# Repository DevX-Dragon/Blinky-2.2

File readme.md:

# Blinky 2.2
This is an blinky board by the NE555P chip. It has an potentiometer to control speed!.

## Layouts

## BOM

| Name | Quanity |
| --- | --- |
| NE555P | 1 |
| CD4017 | 1 |
| LEDs | 10 |
| Headers 1x02 | 1 |
| Headers 1x01 | 1 |
| 50K Potentimeter | 1 |
| 0.01uf Capacitor | 1 |
| 1uf Capacitor | 1 |
| 1K Resistor | 1 |
| 470 Resistor | 1 |

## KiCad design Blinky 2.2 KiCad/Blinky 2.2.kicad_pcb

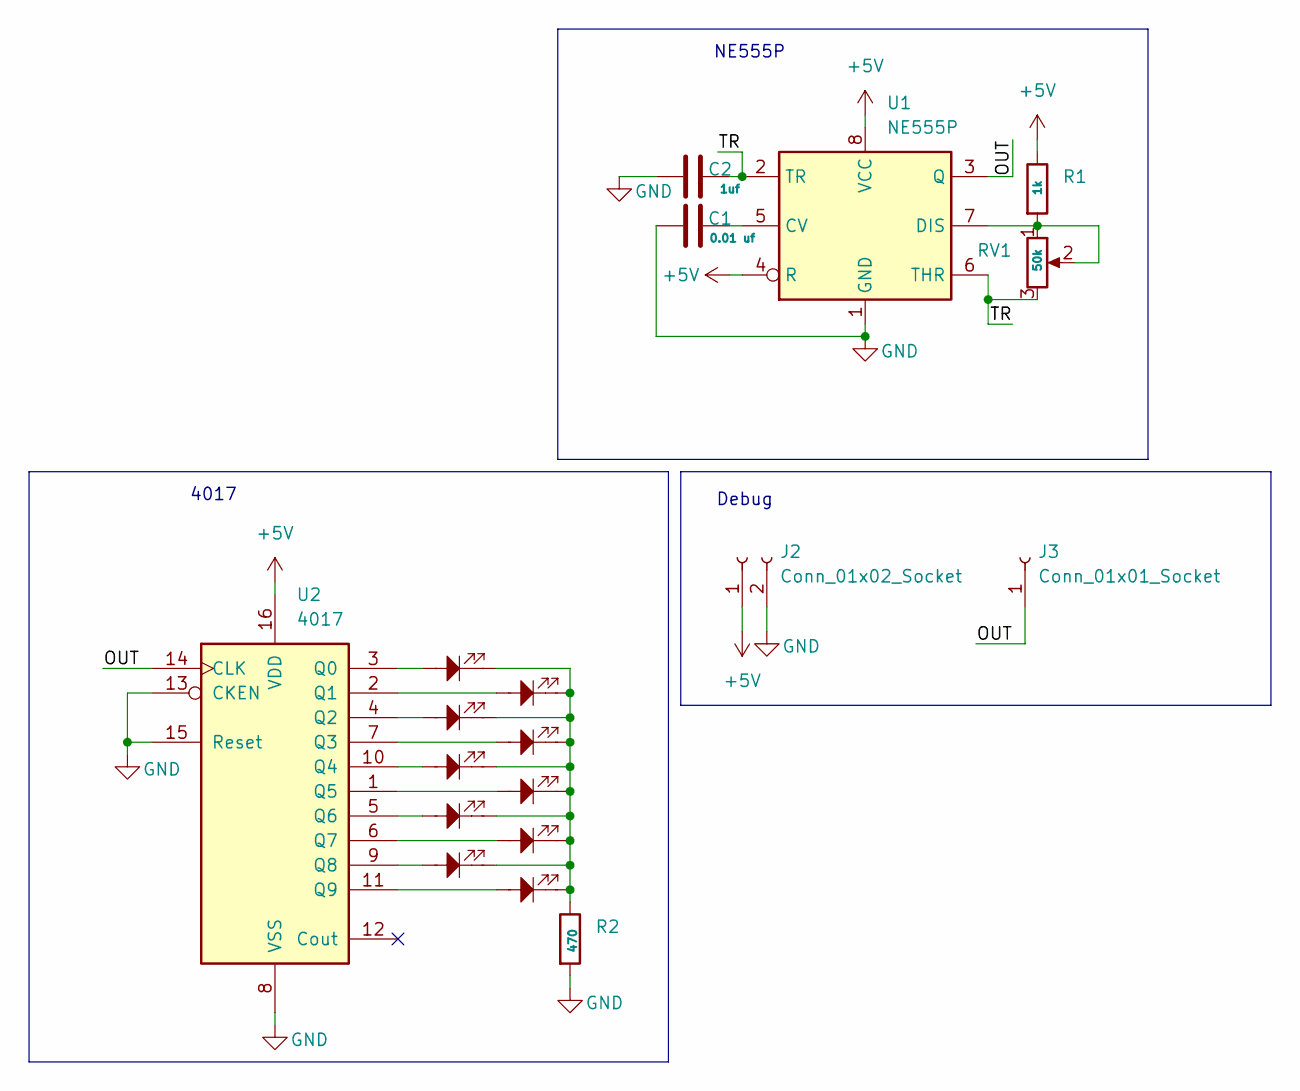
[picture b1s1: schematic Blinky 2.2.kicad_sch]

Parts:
C1: 0.01 uf; C_Disc_D7.5mm_W2.5mm_P5.00mm
C2: 1uf; CP_Radial_D5.0mm_P2.00mm
D1, D2, D3, D4, D5, D6, D7, D8, D9, D13: LED; LED_D3.0mm
J2: Conn_01x02_Socket; PinHeader_1x02_P2.54mm_Vertical
J3: Conn_01x01_Socket; PinHeader_1x01_P2.54mm_Vertical
R1: 1k; R_Axial_DIN0207_L6.3mm_D2.5mm_P7.62mm_Horizontal
R2: 470; R_Axial_DIN0207_L6.3mm_D2.5mm_P7.62mm_Horizontal
RV1: 50k; Potentiometer_Vishay_T93YA_Vertical
U1: NE555P; DIP-8_W7.62mm
U2: 4017; N16

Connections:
+5V: J2.1, R1.1, U1.4 (R), U1.8 (VCC), U2.16 (VDD)
/OUT: J3.1, U1.3 (Q), U2.14 (CLK)
/TR: C2.2, RV1.3, U1.2 (TR), U1.6 (THR)
GND: C1.1, C2.1, J2.2, R2.2, U1.1 (GND), U2.8 (VSS), U2.13 (CKEN), U2.15 (Reset)
unnamed: D1.1, D2.1, D3.1, D4.1, D5.1, D6.1, D7.1, D8.1, D9.1, D13.1, R2.1
unnamed: C1.2, U1.5 (CV)
unnamed: R1.2, RV1.1, RV1.2, U1.7 (DIS)
unnamed: D1.2, U2.3 (Q0)
unnamed: D2.2, U2.2 (Q1)
unnamed: D3.2, U2.4 (Q2)
unnamed: D4.2, U2.7 (Q3)
unnamed: D5.2, U2.10 (Q4)
unnamed: D7.2, U2.1 (Q5)
unnamed: D6.2, U2.5 (Q6)
unnamed: D8.2, U2.6 (Q7)
unnamed: D9.2, U2.9 (Q8)
unnamed: D13.2, U2.11 (Q9)

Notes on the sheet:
Debug
4017
NE555P

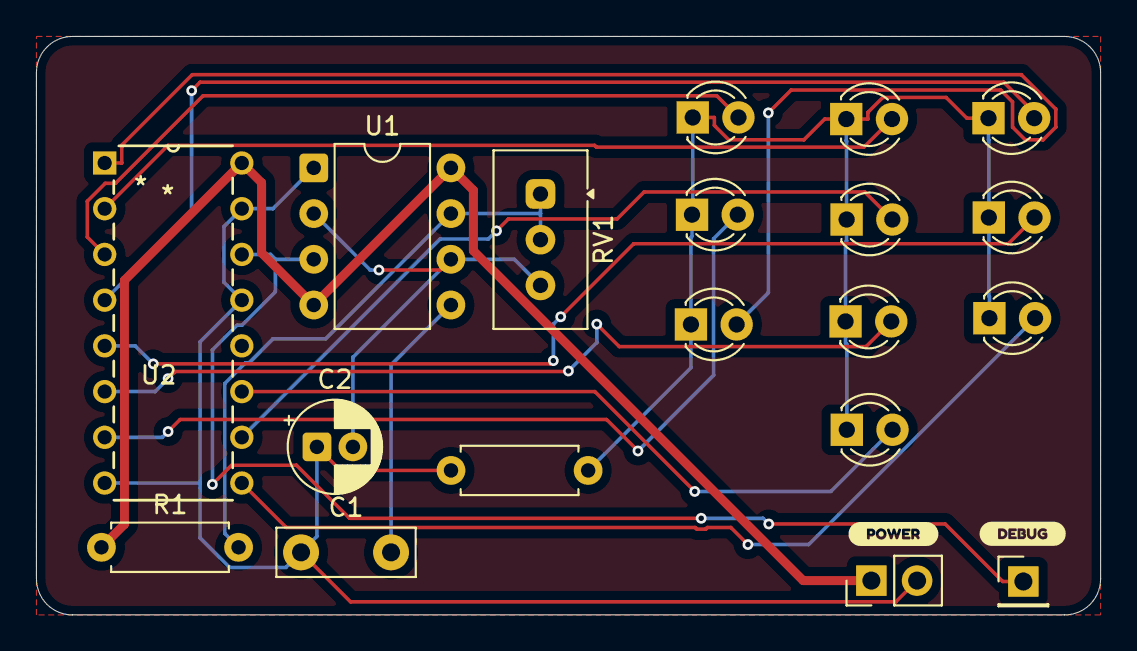
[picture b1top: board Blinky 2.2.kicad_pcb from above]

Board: 2 copper layers, 59.1 x 32.1 mm, 21 parts (0 on the bottom side), 17 nets.

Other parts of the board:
kibuzzard-69CBE313: G***; kibuzzard-69CBE313
kibuzzard-69CBE330: G***; kibuzzard-69CBE330

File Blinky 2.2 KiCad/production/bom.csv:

Designator,Footprint,Quantity,Value,LCSC Part #
C1,C_Disc_D7.5mm_W2.5mm_P5.00mm,1,0.01 uf,
C2,CP_Radial_D5.0mm_P2.00mm,1,1uf,
"D1, D13, D2, D3, D4, D5, D6, D7, D8, D9",LED_D3.0mm,10,LED,
J2,PinHeader_1x02_P2.54mm_Vertical,1,Conn_01x02_Socket,
J3,PinHeader_1x01_P2.54mm_Vertical,1,Conn_01x01_Socket,
R1,R_Axial_DIN0207_L6.3mm_D2.5mm_P7.62mm_Horizontal,1,1k,
R2,R_Axial_DIN0207_L6.3mm_D2.5mm_P7.62mm_Horizontal,1,470,
RV1,Potentiometer_Vishay_T93YA_Vertical,1,50k,
U1,DIP-8_W7.62mm,1,NE555P,
U2,N16,1,4017,

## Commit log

2026-04-01 initial push
2026-04-01 Production Folders
2026-04-01 production
2026-04-01 PCB Update
2026-04-01 images
2026-04-01 readme
